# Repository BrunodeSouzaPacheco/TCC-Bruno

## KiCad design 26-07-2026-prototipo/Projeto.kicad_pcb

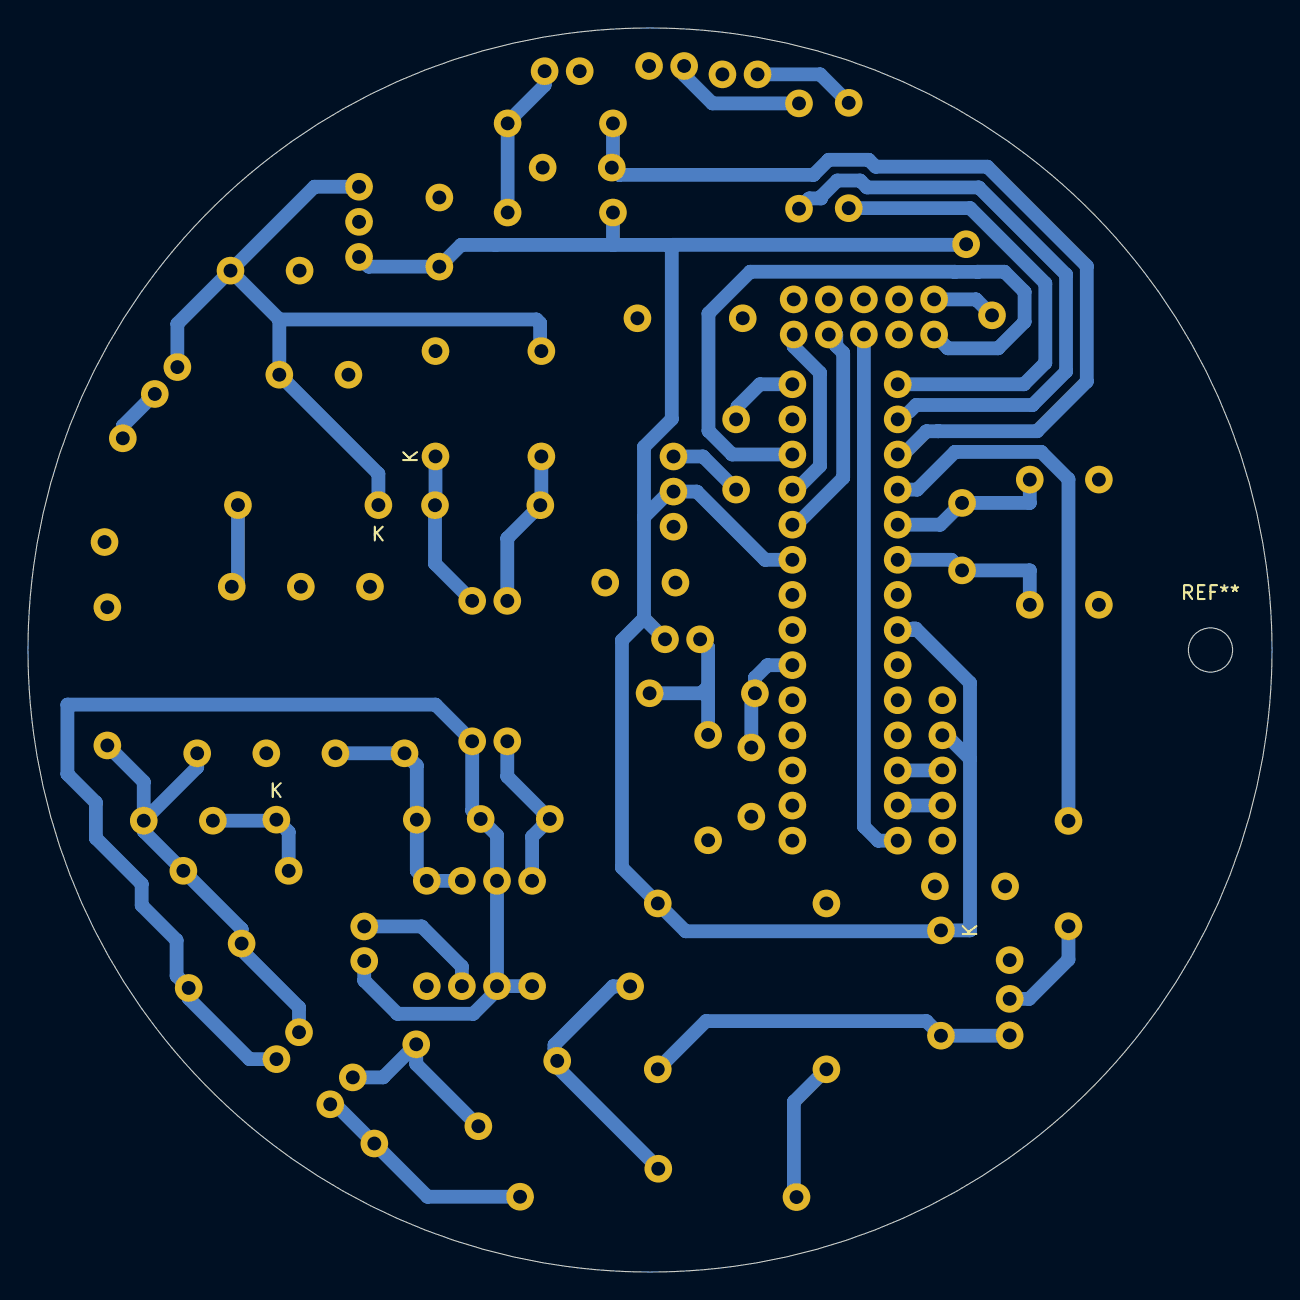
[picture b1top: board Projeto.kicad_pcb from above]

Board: 2 copper layers, 90.0 x 90.0 mm, 52 parts (0 on the bottom side), 37 nets.

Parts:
C1: 6,8uF 400V; CP_Radial_D10.0mm_P5.00mm
C2: 2,7nF; C_Disc_D10.0mm_W2.5mm_P5.00mm
C3: 47uF 25V; C_Disc_D3.0mm_W2.0mm_P2.50mm
C4: 2,2nF; C_Disc_D7.5mm_W5.0mm_P10.00mm
C5: 10nF; C_Disc_D10.0mm_W2.5mm_P5.00mm
C6: 470uF 16V; CP_Radial_D10.0mm_P5.00mm
C7: 100pF; C_Disc_D8.0mm_W2.5mm_P5.00mm
C8, C10: 100nF; C_Disc_D8.0mm_W2.5mm_P5.00mm
C9: 0,47uF; C_Disc_D8.0mm_W2.5mm_P5.00mm
C11, C12: 22pF; C_Disc_D8.0mm_W2.5mm_P5.00mm
D1: LED_VERDE; LED_D3.0mm
D2: LED_AMARELO; LED_D3.0mm
D3: 1N4148; D_DO-41_SOD81_P7.62mm_Horizontal
D4: MB10M; Diode_Bridge_DIP-4_W5.08mm_P2.54mm
D5: 1N4007; D_DO-41_SOD81_P10.16mm_Horizontal
D6: SR160; D_DO-41_SOD81_P10.16mm_Horizontal
D7: 1N6858; D_DO-35_SOD27_P7.62mm_Horizontal
D8: LED; LED_D3.0mm
F1: 1A; Fuse_Bourns_MF-RHT1100
J1: GRAVADOR; PinHeader_2x05_P2.54mm_Vertical
J2: PIR; PinHeader_1x03_P2.54mm_Vertical
J3: Conn_01x03_Socket; Banana_Jack_3Pin
J4: SERIAL; PinHeader_1x05_P2.54mm_Vertical
J5: LDR; PinHeader_1x02_P2.54mm_Vertical
J6: BOTAO; PinHeader_1x02_P2.54mm_Vertical
J7, J7#2, J7#3, J8: JUMPER; TestPoint_Bridge_Pitch5.08mm_Drill0.7mm
J9: JUMPER; TestPoint_Bridge_Pitch7.62mm_Drill1.3mm
K1: G5LE-1; Relay_SPDT_Omron-G5LE-1
Q1: BC547; TO-92_Inline
R1, R2, R6: 10KΩ; R_Axial_DIN0207_L6.3mm_D2.5mm_P7.62mm_Horizontal
R3, R11: 1KΩ; R_Axial_DIN0207_L6.3mm_D2.5mm_P7.62mm_Horizontal
R4, R5: 220Ω; R_Axial_DIN0207_L6.3mm_D2.5mm_P7.62mm_Horizontal
R7: 75KΩ; R_Axial_DIN0207_L6.3mm_D2.5mm_P7.62mm_Horizontal
R8: 390Ω; R_Axial_DIN0207_L6.3mm_D2.5mm_P7.62mm_Horizontal
R9, R10: 1,5KΩ; R_Axial_DIN0207_L6.3mm_D2.5mm_P7.62mm_Horizontal
RV1: Varistor; RV_Disc_D12mm_W3.9mm_P7.5mm
T2: Transformer_1P_1S; trandormador
U1: ATmega328-P; DIP-28_W7.62mm
U2: LM7805_TO220; TO-220-3_Vertical
U3: DK1203; DIP-8_W7.62mm
U4: PC817C; DIP-4_W10.16mm
Y1: Crystal; Crystal_HC49-4H_Vertical

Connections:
+5V: C10.1, D3.1 (K), J1.10, J2.2, J4.2, J5.1, J8.1, J8.2, K1.5, R2.1, U1.7 (VCC), U1.20 (AVCC), U2.3 (VO)
+9V: C6.1, C9.1, D6.1 (K), D8.2 (A), R8.2, U2.1 (VI)
CARGA: J3.3, K1.3
Earth: C1.2, C3.2, C5.2, D4.2 (-), U3.3 (GND), U3.4 (NC), U3.6 (NC), U4.3
FASE: F1.1, J3.2, K1.1
GND: C4.2, C6.2, C7.2, C8.2, C9.2, C10.2, C11.2, C12.2, D1.1 (K), D2.1 (K), D7.2 (A), J1.2, J1.4, J1.6, J1.8, J2.1, J4.5, J6.2, J7.1 (Pin_1_1), J7#2.1 (Pin_1_1), J9.1, J9.2, Q1.3 (E), R1.2, R10.1, T2.3 (SA), U1.8 (GND), U1.22 (GND), U2.2 (GND)
NEUTRO: D4.3, J3.1, RV1.2
unnamed: D1.2 (A), R4.2
unnamed: D2.2 (A), R5.2
unnamed: D3.2 (A), K1.2, Q1.1 (C)
unnamed: C1.1, C2.1, C4.1, D4.1 (+), R7.1, T2.1 (AA)
unnamed: D4.4, F1.2, RV1.1
unnamed: D5.2 (A), T2.2 (AB), T2.6, U3.7 (OC), U3.8 (OC)
unnamed: C2.2, D5.1 (K), R7.2
unnamed: D6.2 (A), T2.4 (SB)
unnamed: D7.1 (K), R9.2, U4.2
unnamed: D8.1 (K), R10.2
unnamed: J5.2, R1.1, R11.1
unnamed: J6.1, R2.2, R3.2
unnamed: Q1.2 (B), R6.1
unnamed: R8.1, R9.1, U4.1
unnamed: C5.1, U3.5 (FB), U4.4
unnamed: C3.1, U3.2 (VCC)
PB0: R5.1, U1.14 (PB0)
PB1: J2.3, J7#3.1 (Pin_1_1), U1.15 (PB1)
PB3: J1.9, U1.17 (PB3)
PB4: J1.1, U1.18 (PB4)
PB5: J1.3, U1.19 (PB5)
PB6: C11.1, U1.9 (XTAL1/PB6), Y1.1
PB7: C12.1, U1.10 (XTAL2/PB7), Y1.2
PC0: C7.1, R11.2, U1.23 (PC0)
PC6: J1.5, U1.1 (~RESET/PC6)
PD0: J4.4, U1.2 (PD0)
PD1: J4.3, U1.3 (PD1)
PD5: R6.2, U1.11 (PD5)
PD6: C8.1, R3.1, U1.12 (PD6)
PD7: R4.1, U1.13 (PD7)
